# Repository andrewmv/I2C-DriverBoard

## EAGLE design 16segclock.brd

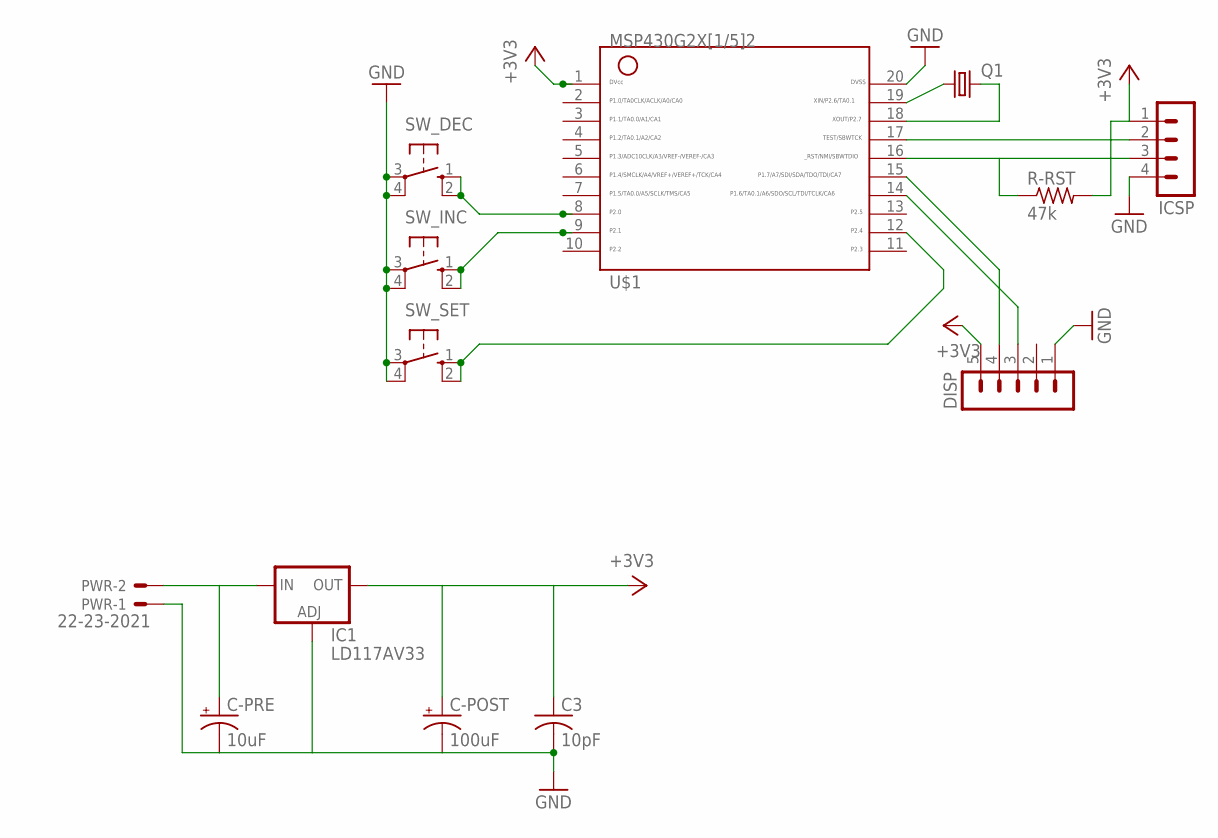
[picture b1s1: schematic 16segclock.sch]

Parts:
C3: 10pF; C0805
C-POST: 100uF; E3,5-8
C-PRE: 10uF; E2,5-6
DISP: MA05-1
IC1: LD117AV33; TO220L1
ICSP: MA04-1
PWR: 22-23-2021
Q1: CRYSTALTC38H; TC38H
R-RST: 47k; R0805
SW_DEC: 10-XX; B3F-10XX
SW_INC: 10-XX; B3F-10XX
SW_SET: 10-XX; B3F-10XX
U$1: G2X[1/5]2---N20; N20

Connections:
!REST: ICSP.3, R-RST.1, U$1.16
+3V3: C3.1, C-POST.+, DISP.5, IC1.2 (OUT), ICSP.1, R-RST.2, U$1.1
GND: C3.2, C-POST.-, C-PRE.-, DISP.1, IC1.1 (ADJ), ICSP.4, PWR.1, SW_DEC.3, SW_DEC.4 (P1), SW_INC.3, SW_INC.4 (P1), SW_SET.3, SW_SET.4 (P1), U$1.20
unnamed: C-PRE.+, IC1.3 (IN), PWR.2
unnamed: Q1.1, U$1.19
unnamed: Q1.2, U$1.18
SCL: DISP.3, U$1.14
SDA: DISP.4, U$1.15
SW_DEC: SW_DEC.1 (S), SW_DEC.2 (S1), U$1.8
SW_INC: SW_INC.1 (S), SW_INC.2 (S1), U$1.9
SW_SET: SW_SET.1 (S), SW_SET.2 (S1), U$1.12
TEST: ICSP.2, U$1.17

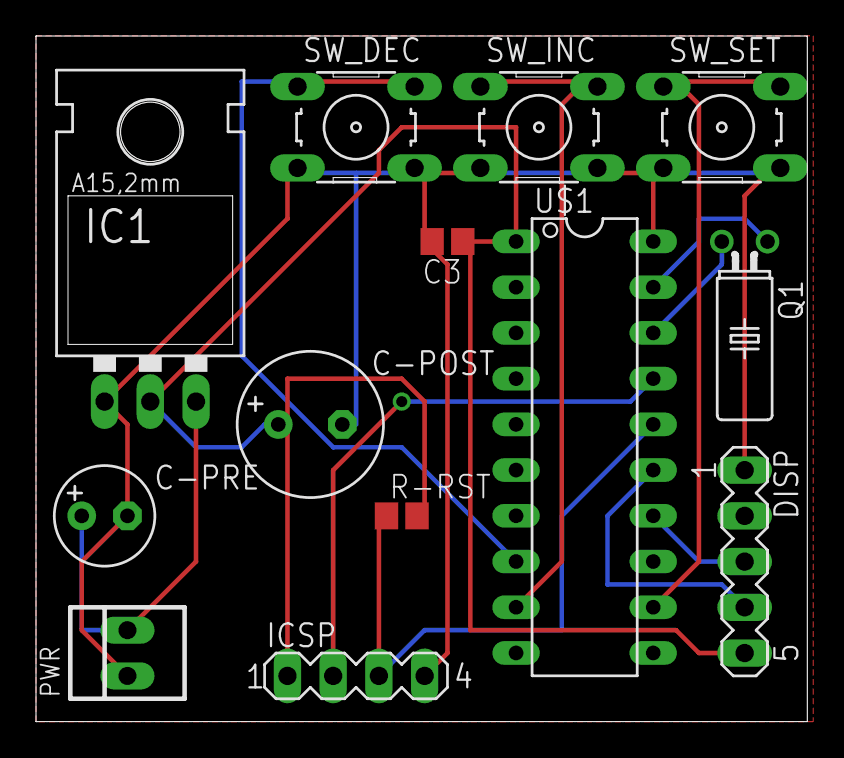
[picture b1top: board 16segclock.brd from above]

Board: 2 copper layers, 42.9 x 38.1 mm, 13 parts (0 on the bottom side), 12 nets.

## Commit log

2016-11-03 :neckbeard: Added .gitattributes & .gitignore files
